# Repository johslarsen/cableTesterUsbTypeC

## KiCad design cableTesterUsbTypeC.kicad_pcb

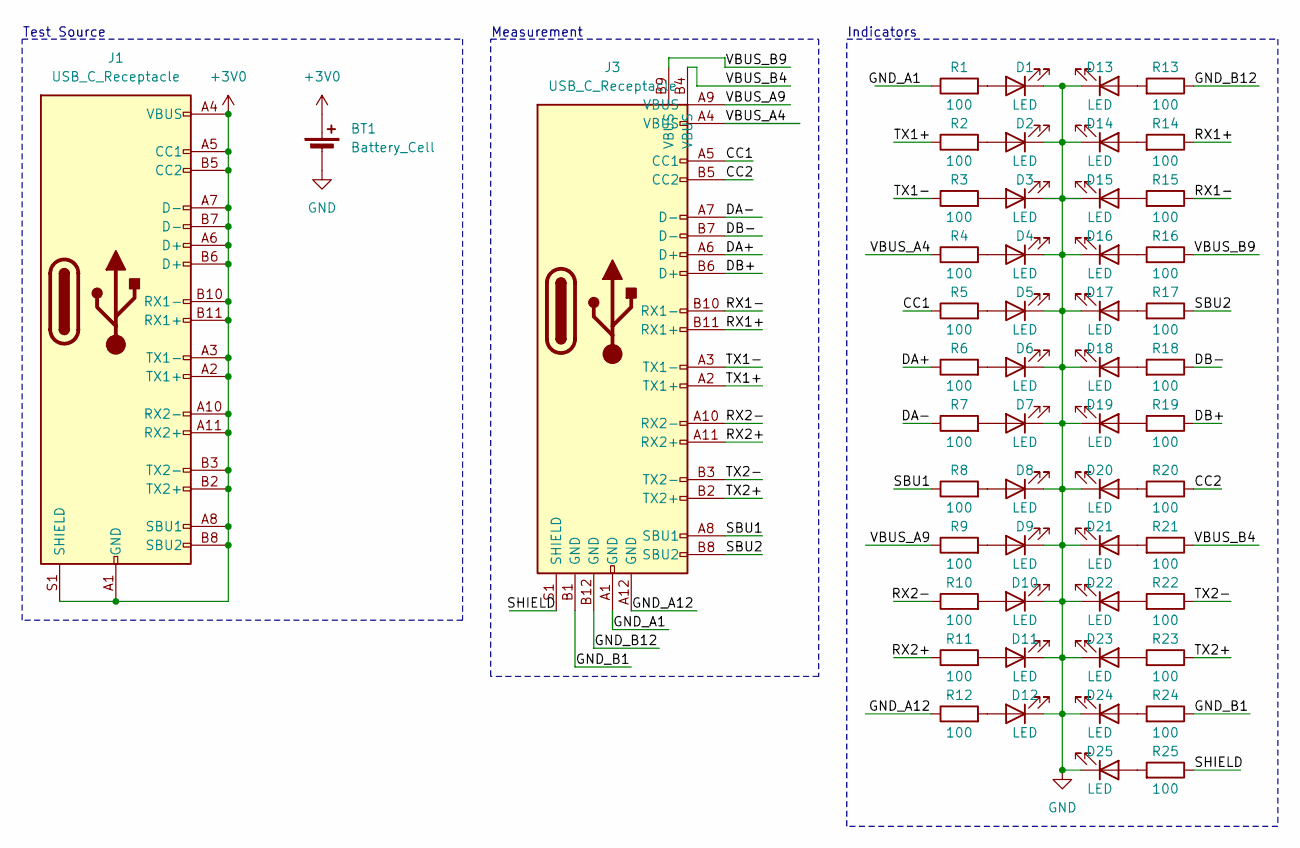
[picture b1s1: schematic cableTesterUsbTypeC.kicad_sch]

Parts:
BT1: Battery_Cell; BatteryHolder_Keystone_1060_1x2032; MPN CR2032-BS-6-1; LCSC C70377
D1, D2, D3, D4, D5, D6, D7, D8, D9, D10, D11, D12, D13, D14, D15, D16, D17, D18, D19, D20, D21, D22, D23, D24, D25: LED; LED_0805_2012Metric; MPN XL-2012UGC; LCSC C965815
J1, J3: USB_C_Receptacle; USB_C_Receptacle_Kinghelm_KH-TYPE-C-JB0.8-24P; MPN KH-TYPE-C-JB0.8-24P; LCSC C2919640
R1, R2, R3, R4, R5, R6, R7, R8, R9, R10, R11, R12, R13, R14, R15, R16, R17, R18, R19, R20, R21, R22, R23, R24, R25: 100; R_0805_2012Metric; MPN FRC0805J101 TS; LCSC C2907294

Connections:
+3V0: BT1.1 (+), J1.A1 (GND), J1.A2 (TX1+), J1.A3 (TX1-), J1.A4 (VBUS), J1.A5 (CC1), J1.A6 (D+), J1.A7 (D-), J1.A8 (SBU1), J1.A9 (VBUS), J1.A10 (RX2-), J1.A11 (RX2+), J1.A12 (GND), J1.B1 (GND), J1.B2 (TX2+), J1.B3 (TX2-), J1.B4 (VBUS), J1.B5 (CC2), J1.B6 (D+), J1.B7 (D-), J1.B8 (SBU2), J1.B9 (VBUS), J1.B10 (RX1-), J1.B11 (RX1+), J1.B12 (GND), J1.S1 (SHIELD)
/CC1: J3.A5 (CC1), R5.1
/CC2: J3.B5 (CC2), R20.1
/DA+: J3.A6 (D+), R6.1
/DA-: J3.A7 (D-), R7.1
/DB+: J3.B6 (D+), R19.1
/DB-: J3.B7 (D-), R18.1
/GND_A1: J3.A1 (GND), R1.1
/GND_A12: J3.A12 (GND), R12.1
/GND_B1: J3.B1 (GND), R24.1
/GND_B12: J3.B12 (GND), R13.1
/RX1+: J3.B11 (RX1+), R14.1
/RX1-: J3.B10 (RX1-), R15.1
/RX2+: J3.A11 (RX2+), R11.1
/RX2-: J3.A10 (RX2-), R10.1
/SBU1: J3.A8 (SBU1), R8.1
/SBU2: J3.B8 (SBU2), R17.1
/SHIELD: J3.S1 (SHIELD), R25.1
/TX1+: J3.A2 (TX1+), R2.1
/TX1-: J3.A3 (TX1-), R3.1
/TX2+: J3.B2 (TX2+), R23.1
/TX2-: J3.B3 (TX2-), R22.1
/VBUS_A4: J3.A4 (VBUS), R4.1
/VBUS_A9: J3.A9 (VBUS), R9.1
/VBUS_B4: J3.B4 (VBUS), R21.1
/VBUS_B9: J3.B9 (VBUS), R16.1
GND: BT1.2 (-), D1.1 (K), D2.1 (K), D3.1 (K), D4.1 (K), D5.1 (K), D6.1 (K), D7.1 (K), D8.1 (K), D9.1 (K), D10.1 (K), D11.1 (K), D12.1 (K), D13.1 (K), D14.1 (K), D15.1 (K), D16.1 (K), D17.1 (K), D18.1 (K), D19.1 (K), D20.1 (K), D21.1 (K), D22.1 (K), D23.1 (K), D24.1 (K), D25.1 (K)
unnamed: D1.2 (A), R1.2
unnamed: D2.2 (A), R2.2
unnamed: D3.2 (A), R3.2
unnamed: D4.2 (A), R4.2
unnamed: D5.2 (A), R5.2
unnamed: D6.2 (A), R6.2
unnamed: D7.2 (A), R7.2
unnamed: D8.2 (A), R8.2
unnamed: D9.2 (A), R9.2
unnamed: D10.2 (A), R10.2
unnamed: D11.2 (A), R11.2
unnamed: D12.2 (A), R12.2
unnamed: D13.2 (A), R13.2
unnamed: D14.2 (A), R14.2
unnamed: D15.2 (A), R15.2
unnamed: D16.2 (A), R16.2
unnamed: D17.2 (A), R17.2
unnamed: D18.2 (A), R18.2
unnamed: D19.2 (A), R19.2
unnamed: D20.2 (A), R20.2
unnamed: D21.2 (A), R21.2
unnamed: D22.2 (A), R22.2
unnamed: D23.2 (A), R23.2
unnamed: D24.2 (A), R24.2
unnamed: D25.2 (A), R25.2

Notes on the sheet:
Test Source
Indicators
Measurement

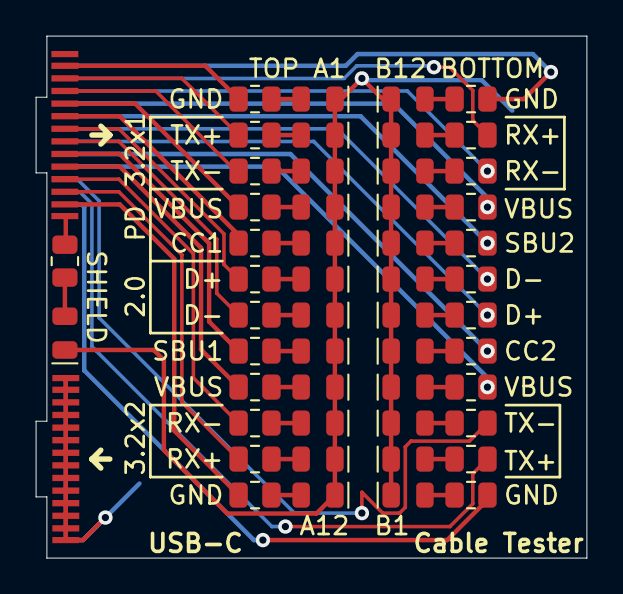
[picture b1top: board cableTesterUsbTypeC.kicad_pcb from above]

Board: 2 copper layers, 30.6 x 29.0 mm, 53 parts (1 on the bottom side), 52 nets.

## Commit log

2023-08-10 Add Connectors.pretty library
2023-08-10 Finished v0.1
2023-08-12 Fix B-side D+ label
2023-08-12 Move indicators 2mm right, making room for protocol group labels
2023-08-12 Add QR/DataMatrix codes to wikipedia page with pin usage tables
    https://en.wikipedia.org/w/index.php?title=USB-C&oldid=1169872296#USB-C
2023-08-12 Add LCSC BOM file to the v0.1 archive
2023-10-22 Add a 3D-printable box to avoid shorting out the battery
